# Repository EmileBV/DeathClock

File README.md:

# DeathClock

This project's goal to make a pocket "watch" that will last and run as long as possible and count down to a set date/time. Using an E-Paper display that will be updated maybe twice per day and a STM32L010xx MCU running on its internal low power clock to achieve very long runtime on a CR2430 coin cell.

This project is still in its very early stages right now, don't expect too much.

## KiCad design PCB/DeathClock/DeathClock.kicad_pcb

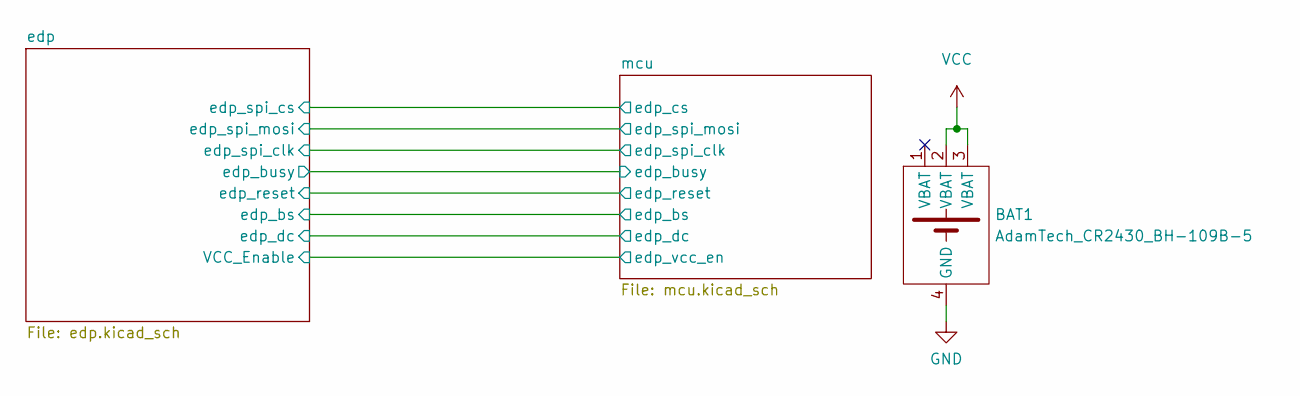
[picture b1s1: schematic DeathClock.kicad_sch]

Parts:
BAT1: AdamTech_CR2430_BH-109B-5; AdamTech_CR2430_BH-109B-5_num_pads

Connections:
GND: BAT1.4 (GND); also elsewhere on the board
VCC: BAT1.2 (VBAT), BAT1.3 (VBAT); also elsewhere on the board

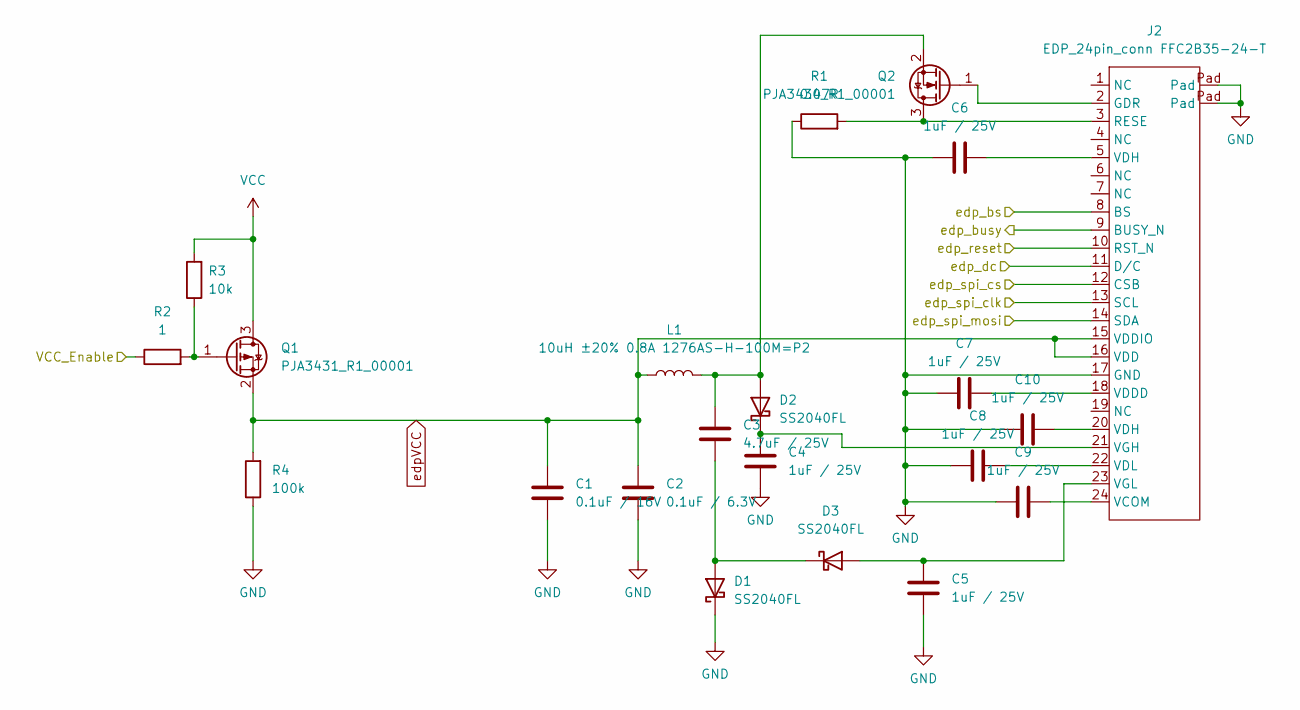
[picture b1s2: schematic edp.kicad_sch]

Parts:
C1: 0.1uF / 16V; C_0402_1005Metric_Pad0.74x0.62mm_HandSolder
C2: 0.1uF / 6.3V; C_0402_1005Metric_Pad0.74x0.62mm_HandSolder
C3: 4.7uF / 25V; C_0402_1005Metric_Pad0.74x0.62mm_HandSolder
C4, C5, C6, C7, C8, C9, C10: 1uF / 25V; C_0402_1005Metric_Pad0.74x0.62mm_HandSolder
D1, D2, D3: SS2040FL; D_SOD-123F
J2: EDP_24pin_conn FFC2B35-24-T; FFC2B35-24-T
L1: 10uH ±20% 0.8A 1276AS-H-100M=P2; L_1210_3225Metric_Pad1.42x2.65mm_HandSolder
Q1: PJA3431_R1_00001; SOT-23
Q2: PJA3430_R1_00001; SOT-23
R1: 0.47R; R_0402_1005Metric_Pad0.72x0.64mm_HandSolder
R2: 1; R_0402_1005Metric_Pad0.72x0.64mm_HandSolder
R3: 10k; R_0402_1005Metric_Pad0.72x0.64mm_HandSolder
R4: 100k; R_0402_1005Metric_Pad0.72x0.64mm_HandSolder

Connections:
/edp/VCC_Enable: R2.1; also elsewhere on the board
/edp/edp_bs: J2.8 (BS); also elsewhere on the board
/edp/edp_busy: J2.9 (BUSY_N); also elsewhere on the board
/edp/edp_dc: J2.11 (D/C); also elsewhere on the board
/edp/edp_reset: J2.10 (RST_N); also elsewhere on the board
/edp/edp_spi_clk: J2.13 (SCL); also elsewhere on the board
/edp/edp_spi_cs: J2.12 (CSB); also elsewhere on the board
/edp/edp_spi_mosi: J2.14 (SDA); also elsewhere on the board
GND: C1.2, C2.2, C4.1, C5.1, C6.1, C7.2, C8.2, C9.2, C10.2, D1.1 (K), J2.17 (GND), J2.Pad, R1.1, R4.1; also elsewhere on the board
unnamed: C3.1, D1.2 (A), D3.1 (K)
unnamed: C3.2, D2.2 (A), L1.2, Q2.2 (S)
unnamed: C4.2, D2.1 (K), J2.21 (VGH)
unnamed: C5.2, D3.2 (A), J2.23 (VGL)
unnamed: C6.2, J2.5 (VDH)
unnamed: C7.1, J2.18 (VDDD)
unnamed: C8.1, J2.22 (VDL)
unnamed: C9.1, J2.24 (VCOM)
unnamed: C10.1, J2.20 (VDH)
unnamed: J2.2 (GDR), Q2.1 (G)
unnamed: J2.3 (RESE), Q2.3 (D), R1.2
unnamed: Q1.1 (G), R2.2, R3.1
VCC: Q1.3 (D), R3.2; also elsewhere on the board
edpVCC: C1.1, C2.1, J2.15 (VDDIO), J2.16 (VDD), L1.1, Q1.2 (S), R4.2

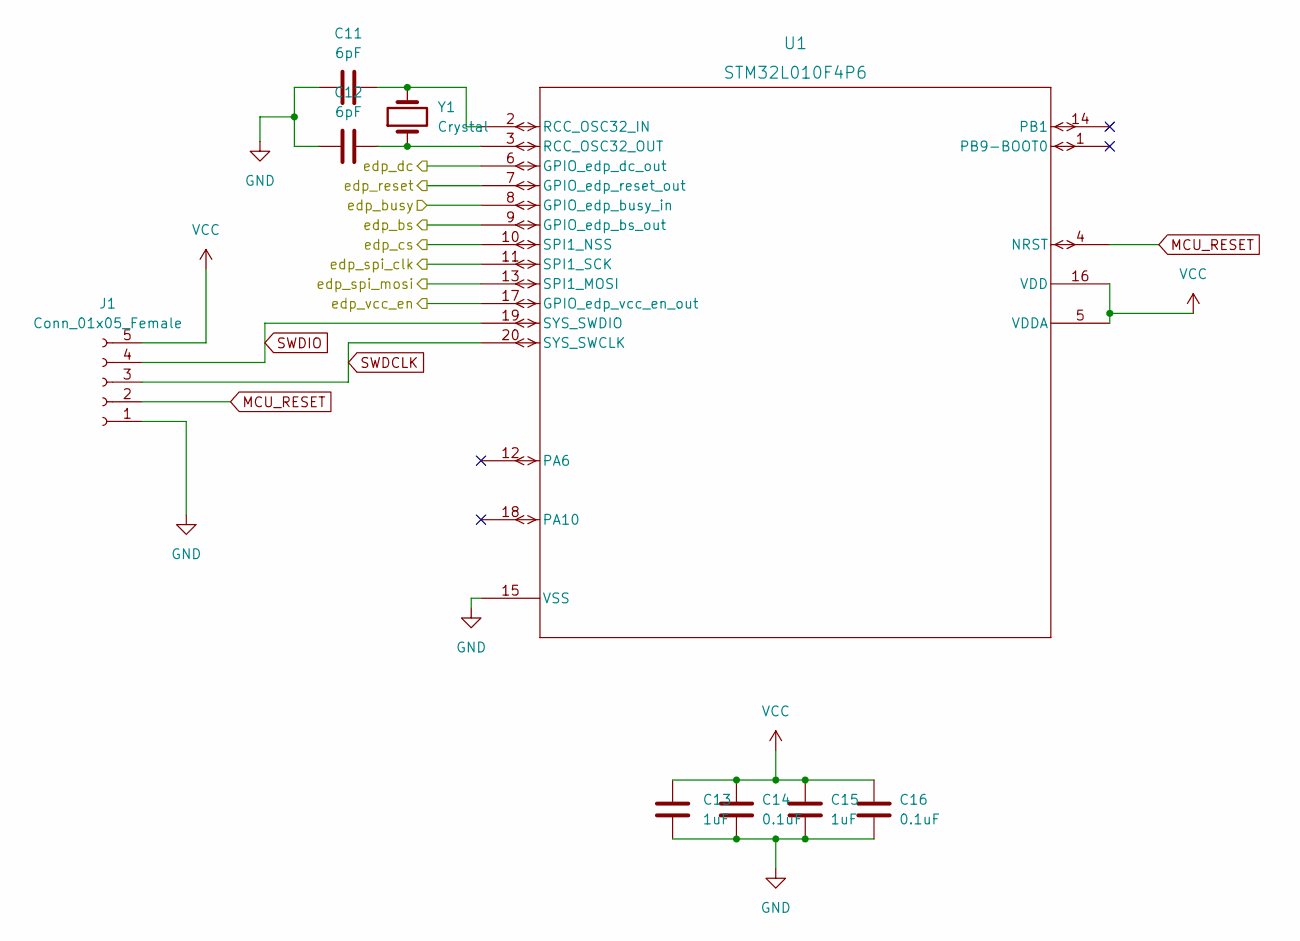
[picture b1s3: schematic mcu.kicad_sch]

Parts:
C11, C12: 6pF; C_0402_1005Metric_Pad0.74x0.62mm_HandSolder
C13, C15: 1uF; C_0402_1005Metric_Pad0.74x0.62mm_HandSolder
C14, C16: 0.1uF; C_0402_1005Metric_Pad0.74x0.62mm_HandSolder
J1: Conn_01x05_Female; PinHeader_1x05_P1.27mm_Vertical
U1: STM32L010F4P6; TSSOP20
Y1: Crystal; Crystal_SMD_2012-2Pin_2.0x1.2mm_HandSoldering

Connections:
/edp/VCC_Enable: U1.17 (GPIO_edp_vcc_en_out); also elsewhere on the board
/edp/edp_bs: U1.9 (GPIO_edp_bs_out); also elsewhere on the board
/edp/edp_busy: U1.8 (GPIO_edp_busy_in); also elsewhere on the board
/edp/edp_dc: U1.6 (GPIO_edp_dc_out); also elsewhere on the board
/edp/edp_reset: U1.7 (GPIO_edp_reset_out); also elsewhere on the board
/edp/edp_spi_clk: U1.11 (SPI1_SCK); also elsewhere on the board
/edp/edp_spi_cs: U1.10 (SPI1_NSS); also elsewhere on the board
/edp/edp_spi_mosi: U1.13 (SPI1_MOSI); also elsewhere on the board
GND: C11.1, C12.1, C13.1, C14.1, C15.1, C16.1, J1.1, U1.15 (VSS); also elsewhere on the board
MCU_RESET: J1.2, U1.4 (NRST)
unnamed: C11.2, U1.2 (RCC_OSC32_IN), Y1.2
unnamed: C12.2, U1.3 (RCC_OSC32_OUT), Y1.1
SWDCLK: J1.3, U1.20 (SYS_SWCLK)
SWDIO: J1.4, U1.19 (SYS_SWDIO)
VCC: C13.2, C14.2, C15.2, C16.2, J1.5, U1.5 (VDDA), U1.16 (VDD); also elsewhere on the board

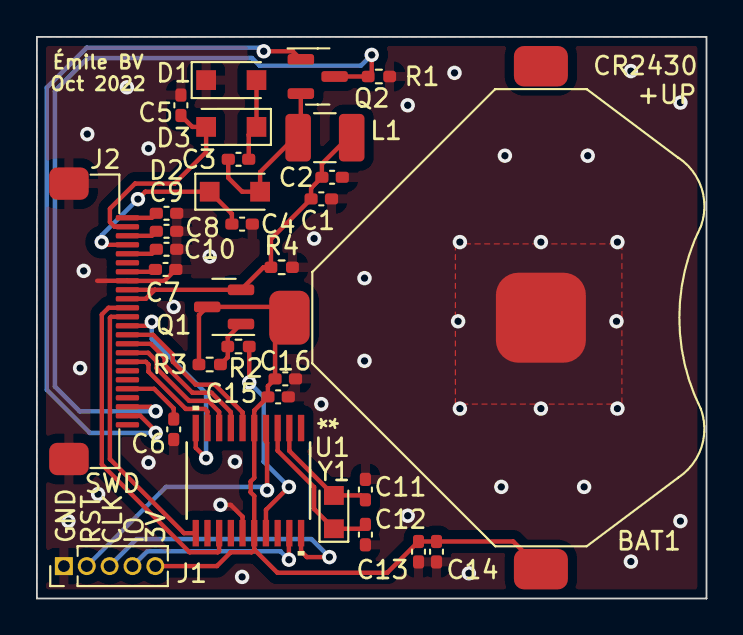
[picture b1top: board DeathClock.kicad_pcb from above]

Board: 2 copper layers, 37.2 x 31.2 mm, 31 parts (0 on the bottom side), 28 nets.

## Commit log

2022-10-09 added gitignore
2022-10-09 added second mosfet to toggle epd power
2022-10-09 made the coin cell symbol 4 pins to make drc happy
2022-10-10 moved some labels around and added SWD header pin names
2022-10-10 added silkscreen stuff for user-friendliness
2022-10-11 moved text around a bit and added snail
2022-10-11 added image of 3D render of PCB
2022-10-12 rework PCB to export step file properly and start of case cad
2022-10-12 case body mostly completed
2025-04-06 updated to kicad 9.0
